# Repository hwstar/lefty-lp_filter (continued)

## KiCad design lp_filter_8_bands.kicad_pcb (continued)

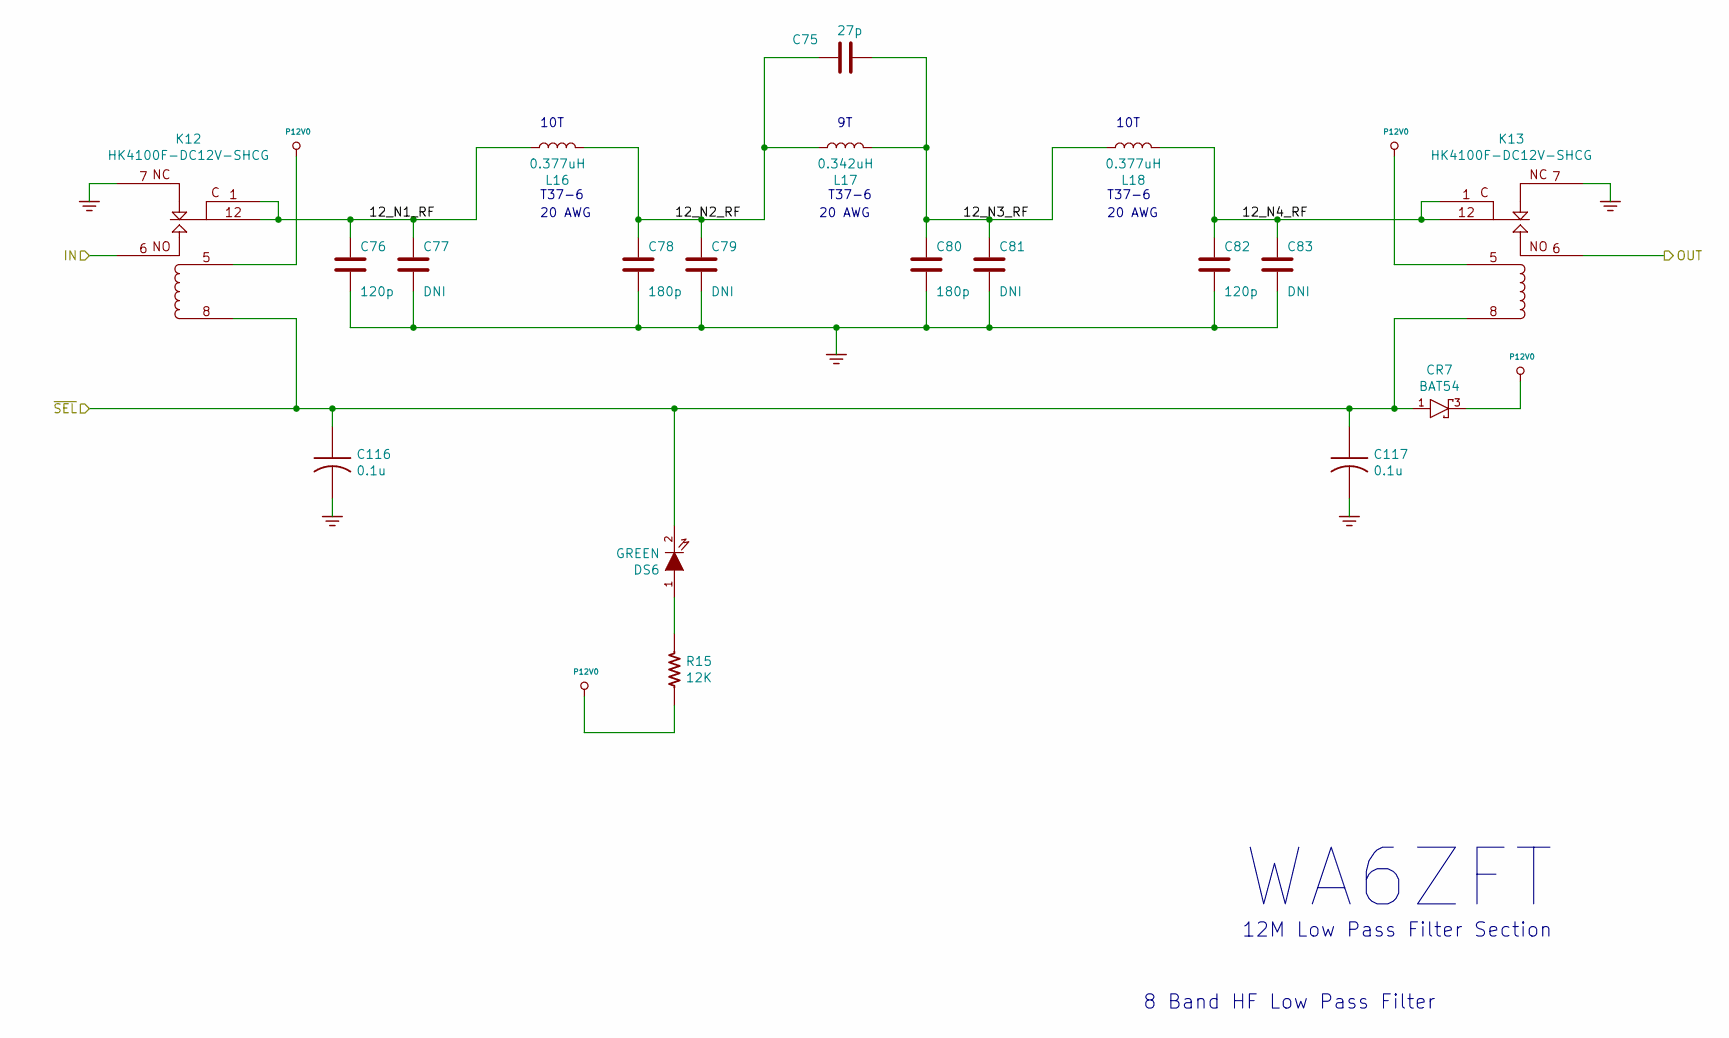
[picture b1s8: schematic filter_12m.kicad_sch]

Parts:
C75: 27p; CC0805; PartNumber 800232-270
C76, C82: 120p; CC0805; PartNumber 800232-121
C77, C79, C81, C83: DNI; CC0805; PartNumber 800XXX-XXX
C78, C80: 180p; CC0805; PartNumber 800232-181
C116, C117: 0.1u; CC0805; PartNumber 800063-XXX
CR7: BAT54; SOT23-3-SAR-V2; PartNumber 800127-101
DS6: GREEN; LED0805; PartNumber 800113-102
K12, K13: HK4100F-DC12V-SHCG; RELAY_HK4100; PartNumber 800231-101
L16, L18: 0.377uH; TOROID_T50_VERT; PartNumber 800234-506
L17: 0.342uH; TOROID_T50_VERT; PartNumber 800234-506
R15: 12K; RC0805; PartNumber 800XXX-XXX

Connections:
/Sheet605F7A0C/ANT_RF: K13.6; also elsewhere on the board
/Sheet605F7A0C/Sheet605F8E24/12_N1_RF: C76.1, C77.1, K12.1, K12.12, L16.1
/Sheet605F7A0C/Sheet605F8E24/12_N2_RF: C75.2, C78.1, C79.1, L16.2, L17.1
/Sheet605F7A0C/Sheet605F8E24/12_N3_RF: C75.1, C80.1, C81.1, L17.2, L18.1
/Sheet605F7A0C/Sheet605F8E24/12_N4_RF: C82.1, C83.1, K13.1, K13.12, L18.2
/Sheet605F7A0C/TXRX_RF: K12.6; also elsewhere on the board
/Sheet605F7A0C/~SEL12: C116.1, C117.1, CR7.1 (A), DS6.2 (K), K12.8, K13.8; also elsewhere on the board
GND: C76.2, C77.2, C78.2, C79.2, C80.2, C81.2, C82.2, C83.2, C116.2, C117.2, K12.7, K13.7; also elsewhere on the board
unnamed: DS6.1 (A), R15.1
P12V0: CR7.3 (C), K12.5, K13.5, R15.2; also elsewhere on the board

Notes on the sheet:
T37-6
8 Band HF Low Pass Filter
WA6ZFT
20 AWG
10T
12M Low Pass Filter Section
10T

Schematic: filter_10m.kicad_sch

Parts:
C84: 27p; CC0805; PartNumber 800232-270
C85, C91: 100p; CC0805; PartNumber 800232-101
C86, C92: DNI; CC0805; PartNumber 800XXX-XXX
C87, C88, C89, C90: 82p; CC0805; PartNumber 800232-820
C118, C119: 0.1u; CC0805; PartNumber 800063-XXX
CR8: BAT54; SOT23-3-SAR-V2; PartNumber 800127-101
DS7: GREEN; LED0805; PartNumber 800113-102
K14, K15: HK4100F-DC12V-SHCG; RELAY_HK4100; PartNumber 800231-101
L19, L21: 0.335uH; TOROID_T50_VERT; PartNumber 800234-506
L20: 0.304uH; TOROID_T50_VERT; PartNumber 800234-506
R16: 12K; RC0805; PartNumber 800XXX-XXX

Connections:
/Sheet605F7A0C/ANT_RF: K15.6; also elsewhere on the board
/Sheet605F7A0C/Sheet605F8E5D/10_N1_RF: C85.1, C86.1, K14.1, K14.12, L19.1
/Sheet605F7A0C/Sheet605F8E5D/10_N2_RF: C84.2, C87.1, C88.1, L19.2, L20.1
/Sheet605F7A0C/Sheet605F8E5D/10_N3_RF: C84.1, C89.1, C90.1, L20.2, L21.1
/Sheet605F7A0C/Sheet605F8E5D/10_N4_RF: C91.1, C92.1, K15.1, K15.12, L21.2
/Sheet605F7A0C/TXRX_RF: K14.6; also elsewhere on the board
/Sheet605F7A0C/~SEL10: C118.1, C119.1, CR8.1 (A), DS7.2 (K), K14.8, K15.8; also elsewhere on the board
GND: C85.2, C86.2, C87.2, C88.2, C89.2, C90.2, C91.2, C92.2, C118.2, C119.2, K14.7, K15.7; also elsewhere on the board
unnamed: DS7.1 (A), R16.1
P12V0: CR8.3 (C), K14.5, K15.5, R16.2; also elsewhere on the board

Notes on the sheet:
20 AWG
10T
WA6ZFT
T37-6
10M Low Pass Filter Section
8 Band HF Low Pass Filter

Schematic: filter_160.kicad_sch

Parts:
C93, C99, C102: 330p; CC0805; PartNumber 800232-331
C94: 47p; CC0805; PartNumber 800232-470
C95, C104: 1500p; CC0805; PartNumber 800232-152
C96, C105: 150p; CC0805; PartNumber 800232-151
C97, C100, C103, C106: DNI; CC0805; PartNumber 800XXX-XXX
C98, C101: 2200p; CC0805; PartNumber 800232-222
C120, C121: 0.1u; CC0805; PartNumber 800063-XXX
CR9: BAT54; SOT23-3-SAR-V2; PartNumber 800127-101
DS8: GREEN; LED0805; PartNumber 800113-102
K16, K17: HK4100F-DC12V-SHCG; RELAY_HK4100; PartNumber 800231-101
L22, L24: 5.21uH; TOROID_T80_VERT; PartNumber 800234-802
L23: 4.73uH; TOROID_T80_VERT; PartNumber 800234-802
R17: 12K; RC0805; PartNumber 800XXX-XXX

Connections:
/Sheet605F7A0C/ANT_RF: K17.6; also elsewhere on the board
/Sheet605F7A0C/Sheet605F91C6/160_N1_RF: C95.1, C96.1, C97.1, K16.1, K16.12, L22.1
/Sheet605F7A0C/Sheet605F91C6/160_N2_RF: C93.2, C94.2, C98.1, C99.1, C100.1, L22.2, L23.1
/Sheet605F7A0C/Sheet605F91C6/160_N3_RF: C93.1, C94.1, C101.1, C102.1, C103.1, L23.2, L24.1
/Sheet605F7A0C/Sheet605F91C6/160_N4_RF: C104.1, C105.1, C106.1, K17.1, K17.12, L24.2
/Sheet605F7A0C/TXRX_RF: K16.6; also elsewhere on the board
/Sheet605F7A0C/~SEL160: C120.1, C121.1, CR9.1 (A), DS8.2 (K), K16.8, K17.8; also elsewhere on the board
GND: C95.2, C96.2, C97.2, C98.2, C99.2, C100.2, C101.2, C102.2, C103.2, C104.2, C105.2, C106.2, C120.2, C121.2, K16.7, K17.7; also elsewhere on the board
unnamed: DS8.1 (A), R17.1
P12V0: CR9.3 (C), K16.5, K17.5, R17.2; also elsewhere on the board

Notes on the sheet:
29T
160M Low Pass Filter Section
T80-2
8 Band HF Low Pass Filter
22 AWG
31T
WA6ZFT

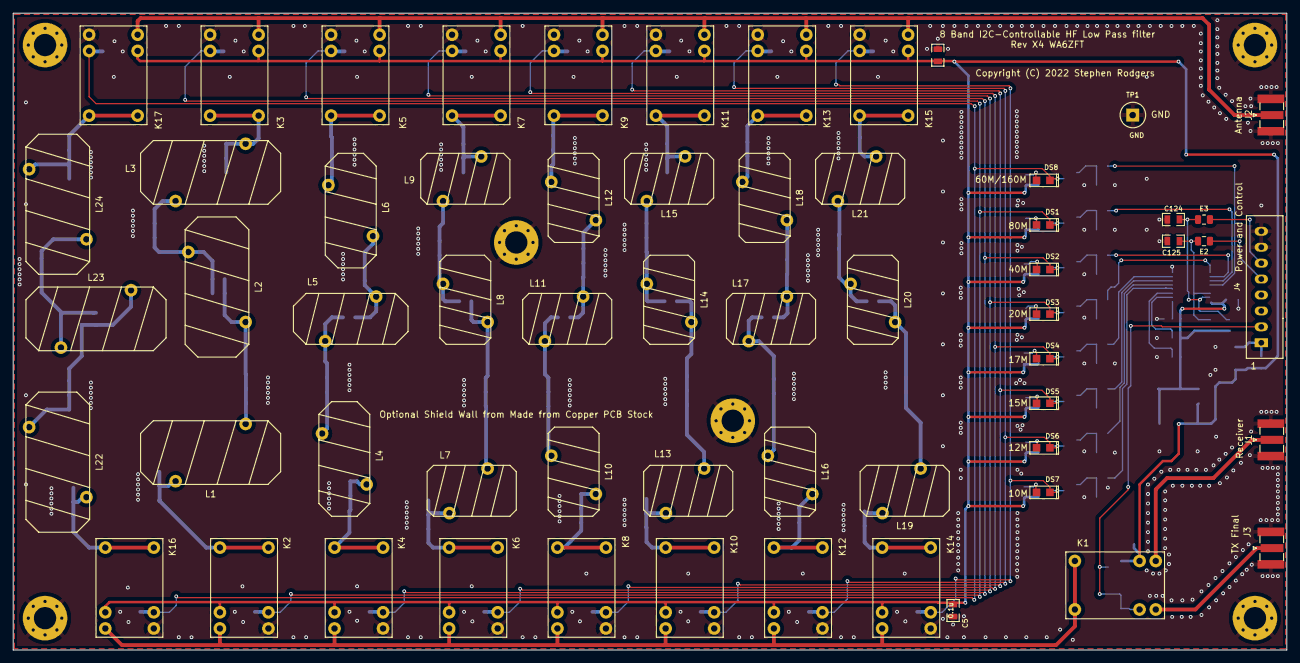
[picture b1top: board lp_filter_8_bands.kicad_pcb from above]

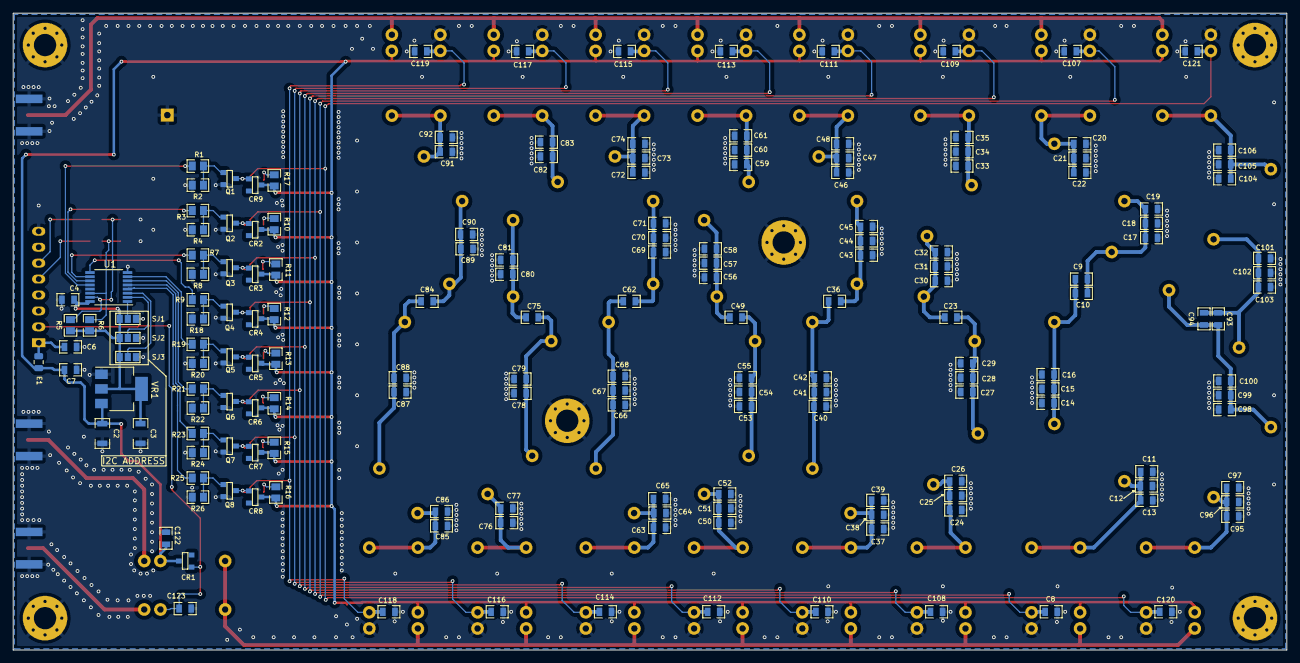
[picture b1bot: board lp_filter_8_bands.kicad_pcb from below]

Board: 2 copper layers, 200.0 x 100.0 mm, 236 parts (170 on the bottom side), 80 nets.

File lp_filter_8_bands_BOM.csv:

Item,Part Number,Qty,Reference(s),Title/Description,Value on Schematic,Manufacturer,Manufacturer Part Number
1,800003-104,23,"C1,C4-C8,C107-C123","CAP,0805,0.1u,25V,X5R",0.1u,Open Market,N/A
2,800232-470,3,"C10,C36,C94","CAP,0805,C0G,47PF,250V",47p,Open Market,N/A
3,800232-222,2,"C98,C101","CAP,0805,C0G,2200PF,250V",2200p,Open Market,N/A
4,800232-331,11,"C24,C27,C28,C30,C31,C33,C40,C43,C93,C99,C102","CAP,0805,C0G,330PF,250V",330p,Open Market,N/A
5,800232-152,2,"C95,C104","CAP,0805,C0G,1500PF,250V",1500p,Open Market,N/A
6,800232-151,7,"C9,C53,C56,C63,C72,C96,C105","CAP,0805,C0G,150PF,250V",150p,Open Market,N/A
7,800232-471,2,"C11,C20","CAP,0805,C0G,470PF,250V",470p,Open Market,N/A
8,800232-391,2,"C12,C21","CAP,0805,C0G,390PF,250V",390p,Open Market,N/A
9,800239-101,2,"C124,C125","CAP,0805,C0G/NPO,100PF,50V",100p,Open Market,N/A
10,800232-122,2,"C14,C17","CAP,0805,C0G,1200PF,250V",1200p,Open Market,N/A
11,800232-101,9,"C15,C18,C23,C25,C34,C54,C57,C85,C91","CAP,0805,C0G,100PF,250V",100p,Open Market,N/A
12,800003-106,2,"C2,C3","CAP,0805,10u,25V,X5R",10u,Open Market,N/A
13,800232-221,4,"C37,C46,C66,C69","CAP,0805,C0G,220PF,250V",220p,Open Market,N/A
14,800232-390,1,C49,"CAP,0805,C0G,39PF,250V",39p,Open Market,N/A
15,800232-820,8,"C50,C51,C59,C60,C87-C90","CAP,0805,C0G,82PF,250V",82p,Open Market,N/A
16,800232-330,1,C62,"CAP,0805,C0G,33PF,250V",33p,Open Market,N/A
17,800232-270,2,"C75,C84","CAP,0805,C0G,27PF,250V",27p,Open Market,N/A
18,800232-121,2,"C76,C82","CAP,0805,C0G,120PF,250V",120p,Open Market,N/A
19,800232-181,2,"C78,C80","CAP,0805,C0G,180PF,250V",180p,Open Market,N/A
20,800127-101,9,CR1-CR9,"DIODE,SCHOTTKY,SGL,SOT-23",BAT54,Diodes Inc.,BAT54-7-F
21,800113-102,8,DS1-DS8,"LED,GREEN,0805",GREEN,Open Market,N/A
22,800245-601,3,E1-E3,"FERRITE,CHIP,0805,600 ohm,100MHz,500mA",FB0805,Sunlord,GZ2012U601TF
23,800233-101,3,J1-J3,"CONN,SOC,SMA,LAUNCH,0.062 PCB",CONN_SMA_LAUNCH,Kinghelm,KH-SMA-KE8-G
24,800114-108,1,J4,"CONN,HDR,SHROUDED,8 CKT,5MM,XH SERIES",CONN8,JST,B8B-XH-A
25,800231-101,17,K1-K17,"RELAY,SPDT,12V,3A",HK4100F-DC12V-SHCG,HUIKE,HK4100F-DC12V-SHCG
26,800234-802,6,"L1-L3,L22-L24","TOROID,POWDERED_IRON,T80-2",2.68uH,Open Market,T80-2
27,800234-506,15,L7-L21,"TOROID,POWDERED_IRON,T50-6",0.67uH,Open Market,T50-6
28,800234-686,3,L4-L6,"TOROID,POWDERED_IRON,T68-6",1.34uH,Open Market,T68-6
29,800110-101,8,Q1-Q8,"XSTR,GP,NPN,40V,SOT23",MMBT4401,Fairchild Semiconductor,MMBT4401
30,800235-222,8,"R1,R3,R7,R9,R19,R21,R23,R25","RES,0805,2.2K,1%",2.2K,Open Market,N/A
31,800235-123,8,R10-R17,"RES,0805,12K,1%",12K,Open Market,N/A
32,800235-102,8,"R2,R4,R8,R18,R20,R22,R24,R26","RES,0805,1.0K,1%",1K,Open Market,N/A
33,800235-103,2,"R5,R6","RES,0805,10K,1%",10K,Open Market,N/A
34,800116-101,1,TP1,"CONN,HDR,1CKT,0.1PITCH,BERGSTRIP",GND,Open Market,N/A
35,800237-101,1,U1,"IC, I2C BUS EXPANDER, 8 BIT, TSSOP16",PCA9554APW,NEXPERIA,PCA9554APW
36,800121-101,1,VR1,"IC,VREG,3.3V,1A,SOT-223",NCP1117ST33,On Semiconductor,NCP1117ST33T3G
37,XXXXXX-XXX,38,"C100,C103,C106,C13,C16,C19,C22,C26,C29,C32,C35,C38,C39,C41,C42,C44,C45,C47,C48,C52,C55,C58,C61,C64,C65,C67,C68,C70,C71,C73,C74,C77,C79,C81,C83,C86,C92,C97",DNI,DNI,DNI,DNI

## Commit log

2022-05-21 Add .pdf schematic
2022-05-21 Add licence and readme
2022-05-21 Update README.md. Add pic
